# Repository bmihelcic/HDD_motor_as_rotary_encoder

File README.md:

# HDD_motor_as_rotary_encoder
Hacking old computer hard disk drive motor to suit as an rotary encoder

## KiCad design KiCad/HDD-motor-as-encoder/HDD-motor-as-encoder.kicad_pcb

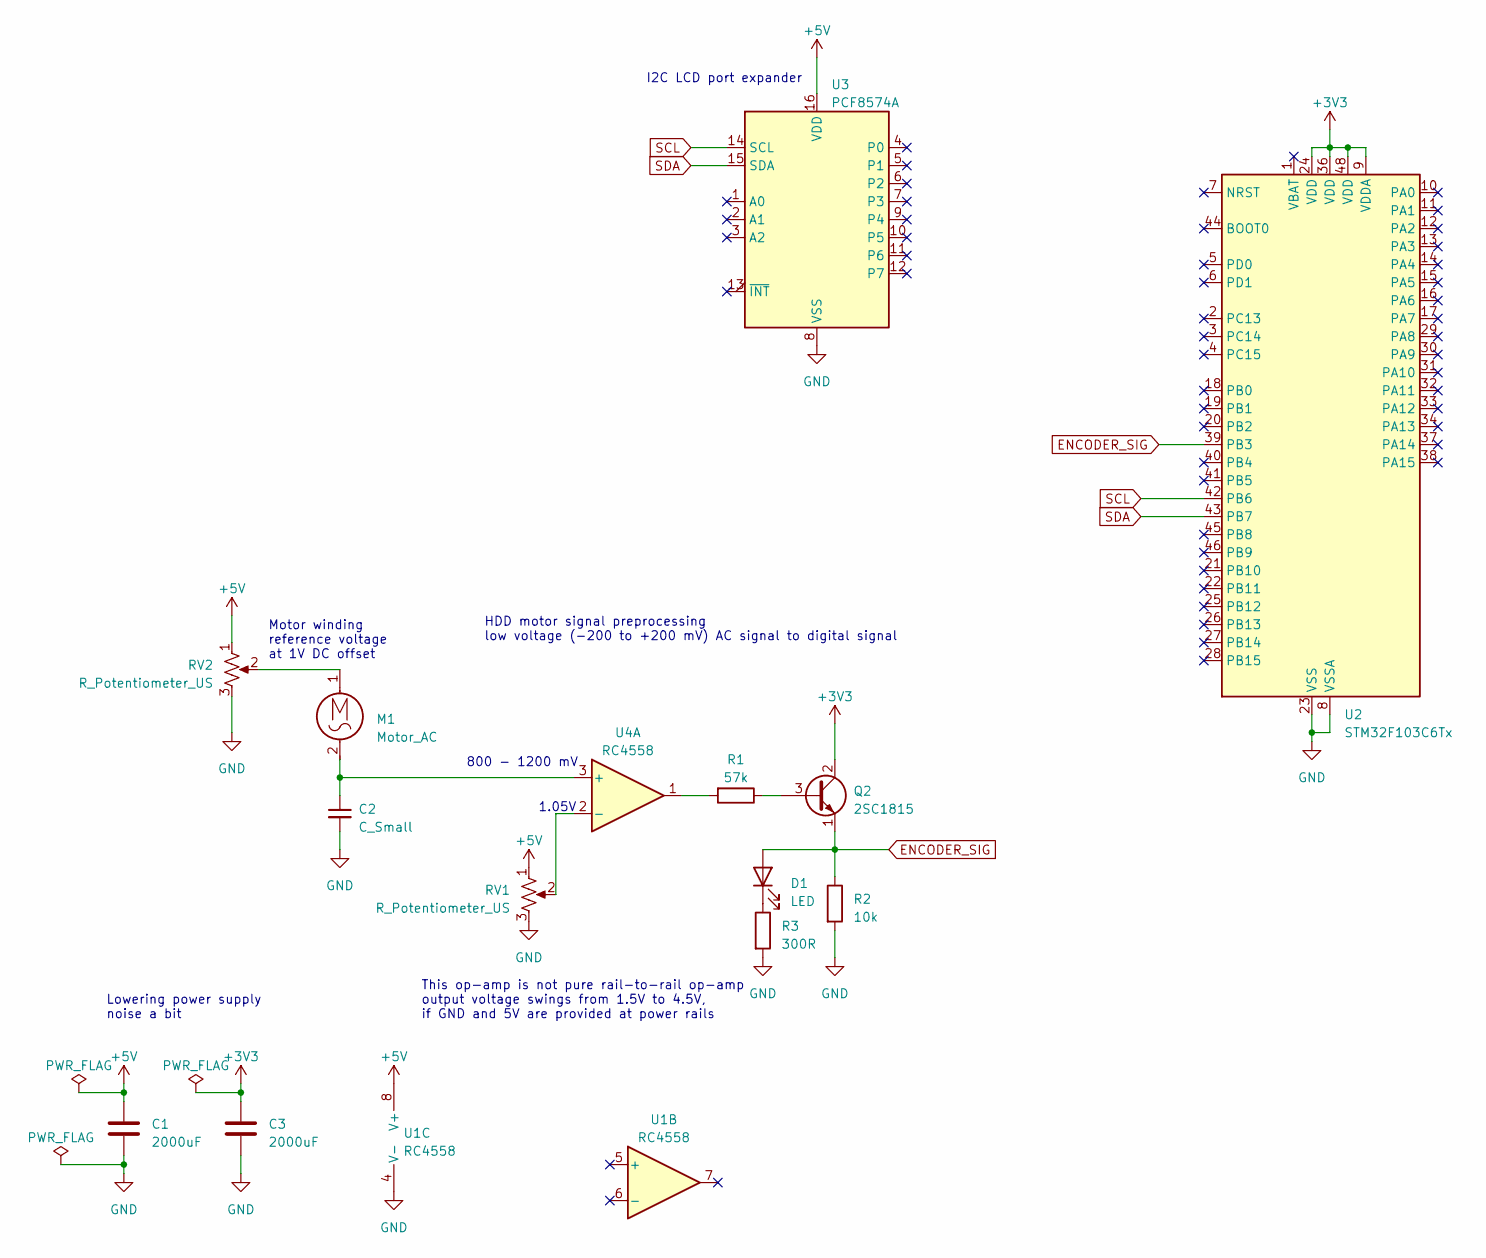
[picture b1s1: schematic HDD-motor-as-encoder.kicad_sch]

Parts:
C1, C3: 2000uF
C2: C_Small
D1: LED
M1: Motor_AC
Q2: 2SC1815
R1: 57k
R2: 10k
R3: 300R
RV1, RV2: R_Potentiometer_US
U1, U4: RC4558
U2: STM32F103C6Tx
U3: PCF8574A

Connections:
+3V3: C3.1, Q2.2 (C), U2.9 (VDDA), U2.24 (VDD), U2.36 (VDD), U2.48 (VDD)
+5V: C1.1, RV1.1, RV2.1, U1.8 (V+), U3.16 (VDD)
ENCODER_SIG: D1.2 (A), Q2.1 (E), R2.1, U2.39 (PB3)
GND: C1.2, C2.2, C3.2, R2.2, R3.2, RV1.3, RV2.3, U1.4 (V-), U2.8 (VSSA), U2.23 (VSS), U2.35 (VSS), U2.47 (VSS), U3.8 (VSS)
unnamed: D1.1 (K), R3.1
unnamed: M1.1, RV2.2
unnamed: Q2.3 (B), R1.1
unnamed: R1.2, U4.1
unnamed: C2.1, M1.2, U4.3 (+)
unnamed: RV1.2, U4.2 (-)
SCL: U2.42 (PB6), U3.14 (SCL)
SDA: U2.43 (PB7), U3.15 (SDA)

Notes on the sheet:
This op-amp is not pure rail-to-rail op-amp output voltage swings from 1.5V to 4.5V, if GND and 5V are provided at power rails
800 - 1200 mV
Lowering power supply noise a bit
1.05V
HDD motor signal preprocessing low voltage (-200 to +200 mV) AC signal to digital signal
I2C LCD port expander
Motor winding reference voltage at 1V DC offset

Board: 2 copper layers, 15 parts (0 on the bottom side), 12 nets, no tracks yet.

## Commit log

2023-03-12 Initial Hdd motor as rotary encoder project files (working demo)
    Basic demo, read encoder pulses and output a counter value to LCD via I2C
2023-03-12 Add front project picture
